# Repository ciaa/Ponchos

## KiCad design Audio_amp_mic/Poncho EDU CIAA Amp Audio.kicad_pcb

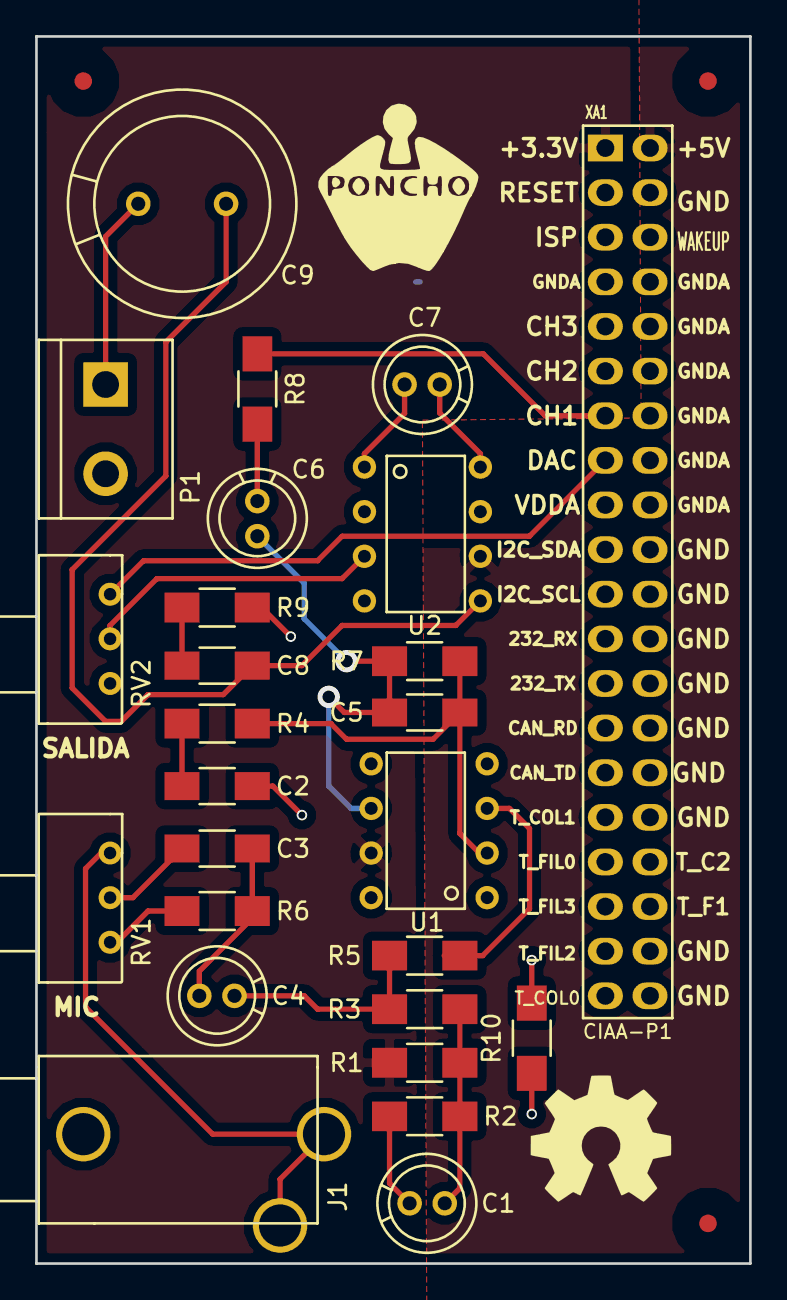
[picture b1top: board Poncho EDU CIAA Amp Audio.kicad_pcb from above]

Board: 2 copper layers, 40.6 x 69.8 mm, 30 parts (0 on the bottom side), 22 nets.

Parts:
C1: 100 uF; Kemet_ESH106M050AC3AA
C2: 22 uF; C_1206_HandSoldering
C3: 0,022 uF; C_1206_HandSoldering
C4: 1 uF; Kemet_ESH106M050AC3AA
C5: 100pF; C_1206_HandSoldering
C6, C7: 10 uF; Kemet_ESH106M050AC3AA
C8: 0,047 uF; C_1206_HandSoldering
C9: 270 uF; C_Kemet_ESY277M063AL3AA
F1, F2, F3: FIDUCIAL; Fiducial_1mm
G101: Logo_OSHWA
J1: JACK_2P; Conector_mini_Plug
P1: CONN_01X02; bornier2
R1, R2, R8: 4,7k; R_1206_HandSoldering
R3, R7: 47k; R_1206_HandSoldering
R4: 560; R_1206_HandSoldering
R5: 1k; R_1206_HandSoldering
R6: 15k; R_1206_HandSoldering
R9: 10; R_1206_HandSoldering
R10: 0; R_1206_HandSoldering
RV1: 20k; POT_20K_0.25W_Bourns_3310C
RV2: 10 k; POT_20K_0.25W_Bourns_3310C
U1: LM741; LM741_Texas_Instruments
U2: LM386; LM741_Texas_Instruments
XA1: Conn_Poncho2P_2x_20x2; Conn_Poncho_Derecha

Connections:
+3.3V: R1.1, U1.7, XA1.1
+5V: U2.6, XA1.2
/ADC: R8.1, XA1.13
/DAC: RV2.1, XA1.15
GND: R10.2, U1.4, U2.4, XA1.4, XA1.20, XA1.22, XA1.24, XA1.26, XA1.28, XA1.30, XA1.32, XA1.38, XA1.40
GNDA: C1.2, C2.2, J1.3, P1.2, R2.2, R6.1, R9.2, R10.1, RV1.3, RV2.3, U2.2, XA1.7, XA1.8, XA1.10, XA1.12, XA1.14, XA1.16, XA1.18
unnamed: C1.1, R1.2, R2.1, R3.2
unnamed: C2.1, R4.2
unnamed: C3.1, RV1.2
unnamed: C3.2, C4.1, R6.2
unnamed: C4.2, R3.1, R5.2
unnamed: C5.1, C6.1, R7.1, U1.6
unnamed: C5.2, R4.1, R7.2, U1.2
unnamed: C6.2, R8.2
unnamed: C7.1, U2.1
unnamed: C7.2, U2.8
unnamed: C8.1, C9.1, U2.5
unnamed: C8.2, R9.1
unnamed: C9.2, P1.1
unnamed: J1.1, J1.2, RV1.1
unnamed: R5.1, U1.3
unnamed: RV2.2, U2.3

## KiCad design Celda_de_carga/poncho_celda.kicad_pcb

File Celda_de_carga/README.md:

# LoadCellShield

Proyecto de modulo externo (Poncho) de una celda de carga para la EDU-CIAA, durante el curso de Diseño de PCB del CESE.

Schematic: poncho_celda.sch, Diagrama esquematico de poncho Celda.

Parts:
DS1: LCD16X2; LCD16x2
F1, F2, F3: FIDUCIAL; Fiducial_1mm
R7: 220; R_1206_HandSoldering
RV1: 10K; POT_SMD

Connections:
+5V: DS1.2, DS1.15, RV1.1; also elsewhere on the board
/Conector-EDU_CIAA/lcd1: DS1.11; also elsewhere on the board
/Conector-EDU_CIAA/lcd2: DS1.12; also elsewhere on the board
/Conector-EDU_CIAA/lcd3: DS1.13; also elsewhere on the board
/Conector-EDU_CIAA/lcd4: DS1.14; also elsewhere on the board
/Conector-EDU_CIAA/lcdEn: DS1.6; also elsewhere on the board
/Conector-EDU_CIAA/lcdRs: DS1.4; also elsewhere on the board
GND: DS1.1, DS1.5, DS1.7, DS1.8, DS1.9, DS1.10, R7.2, RV1.3; also elsewhere on the board
unnamed: DS1.3, RV1.2
unnamed: DS1.16, R7.1

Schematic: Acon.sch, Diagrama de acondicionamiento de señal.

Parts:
C1, C3: 1nF; C_0603_HandSoldering
C2: 10nF; C_0603_HandSoldering
C4, C5, C6: 100nF; C_0805_HandSoldering
R1, R2, R5, R6: 1k; R_1206_HandSoldering
R3: 499; R_1206_HandSoldering
R4: 51k; R_1206_HandSoldering
U1: AD620; SOIC-8
U2: REF1004-2.5; SOIC-8
U3: ADS1113/15; TSSOP-10_3x3mm_Pitch0.5mm
conn1: CONN_CELDA; bornier4

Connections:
+3.3V: R5.1, R6.1; also elsewhere on the board
+5V: C4.1, C5.1, C6.1, R4.2, U1.7, U3.8, conn1.1; also elsewhere on the board
/Adqui_Celda/alert: U3.2; also elsewhere on the board
/Adqui_Celda/scl: R5.2, U3.10; also elsewhere on the board
/Adqui_Celda/sda: R6.2, U3.9; also elsewhere on the board
GND: C1.1, C3.2, C4.2, C5.2, C6.2, U1.4, U2.4, U3.1, U3.3, conn1.4; also elsewhere on the board
unnamed: C1.2, C2.1, R1.1, U1.3
unnamed: C2.2, C3.1, R2.1, U1.2
unnamed: R1.2, conn1.2
unnamed: R2.2, conn1.3
unnamed: R3.1, U1.8
unnamed: R3.2, U1.1
unnamed: R4.1, U2.8
unnamed: U1.5, U2.6
unnamed: U1.6, U3.4

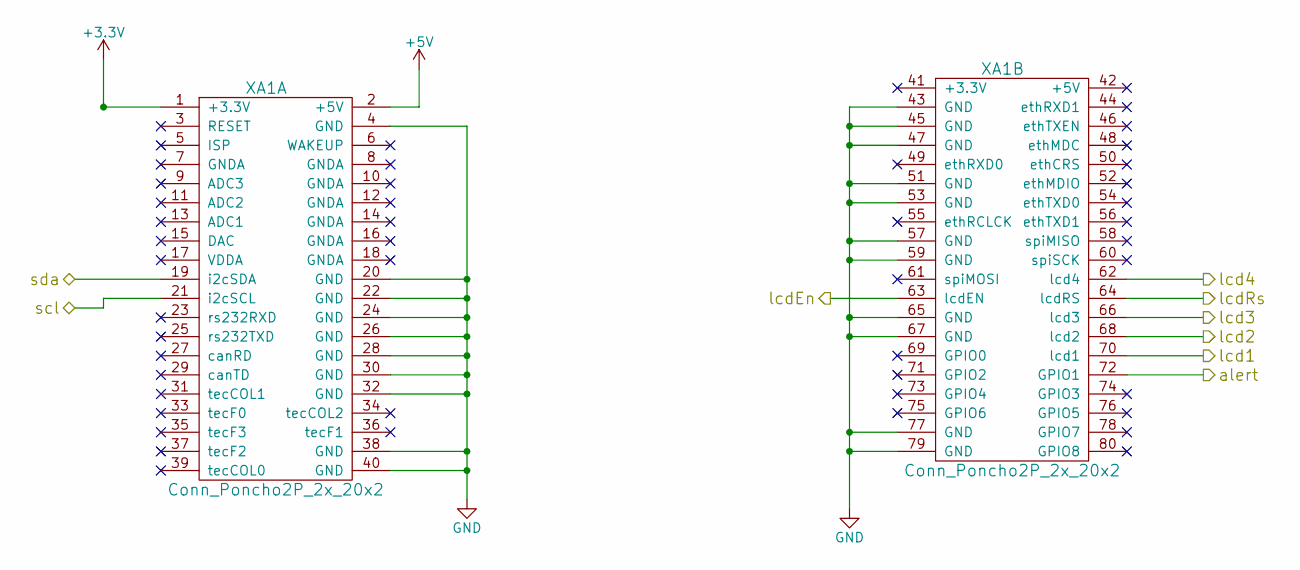
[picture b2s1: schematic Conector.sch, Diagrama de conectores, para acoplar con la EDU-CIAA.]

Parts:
XA1: Conn_Poncho2P_2x_20x2; Conn_Poncho_SinBorde

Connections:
+3.3V: XA1.1 (+3.3V); also elsewhere on the board
+5V: XA1.2 (+5V); also elsewhere on the board
/Adqui_Celda/alert: XA1.72 (GPIO1); also elsewhere on the board
/Adqui_Celda/scl: XA1.21 (i2cSCL); also elsewhere on the board
/Adqui_Celda/sda: XA1.19 (i2cSDA); also elsewhere on the board
/Conector-EDU_CIAA/lcd1: XA1.70 (lcd1); also elsewhere on the board
/Conector-EDU_CIAA/lcd2: XA1.68 (lcd2); also elsewhere on the board
/Conector-EDU_CIAA/lcd3: XA1.66 (lcd3); also elsewhere on the board
/Conector-EDU_CIAA/lcd4: XA1.62 (lcd4); also elsewhere on the board
/Conector-EDU_CIAA/lcdEn: XA1.63 (lcdEN); also elsewhere on the board
/Conector-EDU_CIAA/lcdRs: XA1.64 (lcdRS); also elsewhere on the board
GND: XA1.4 (GND), XA1.20 (GND), XA1.22 (GND), XA1.24 (GND), XA1.26 (GND), XA1.28 (GND), XA1.30 (GND), XA1.32 (GND), XA1.38 (GND), XA1.40 (GND), XA1.43 (GND), XA1.45 (GND), XA1.47 (GND), XA1.51 (GND), XA1.53 (GND), XA1.57 (GND), XA1.59 (GND), XA1.65 (GND), XA1.67 (GND), XA1.77 (GND), XA1.79 (GND); also elsewhere on the board

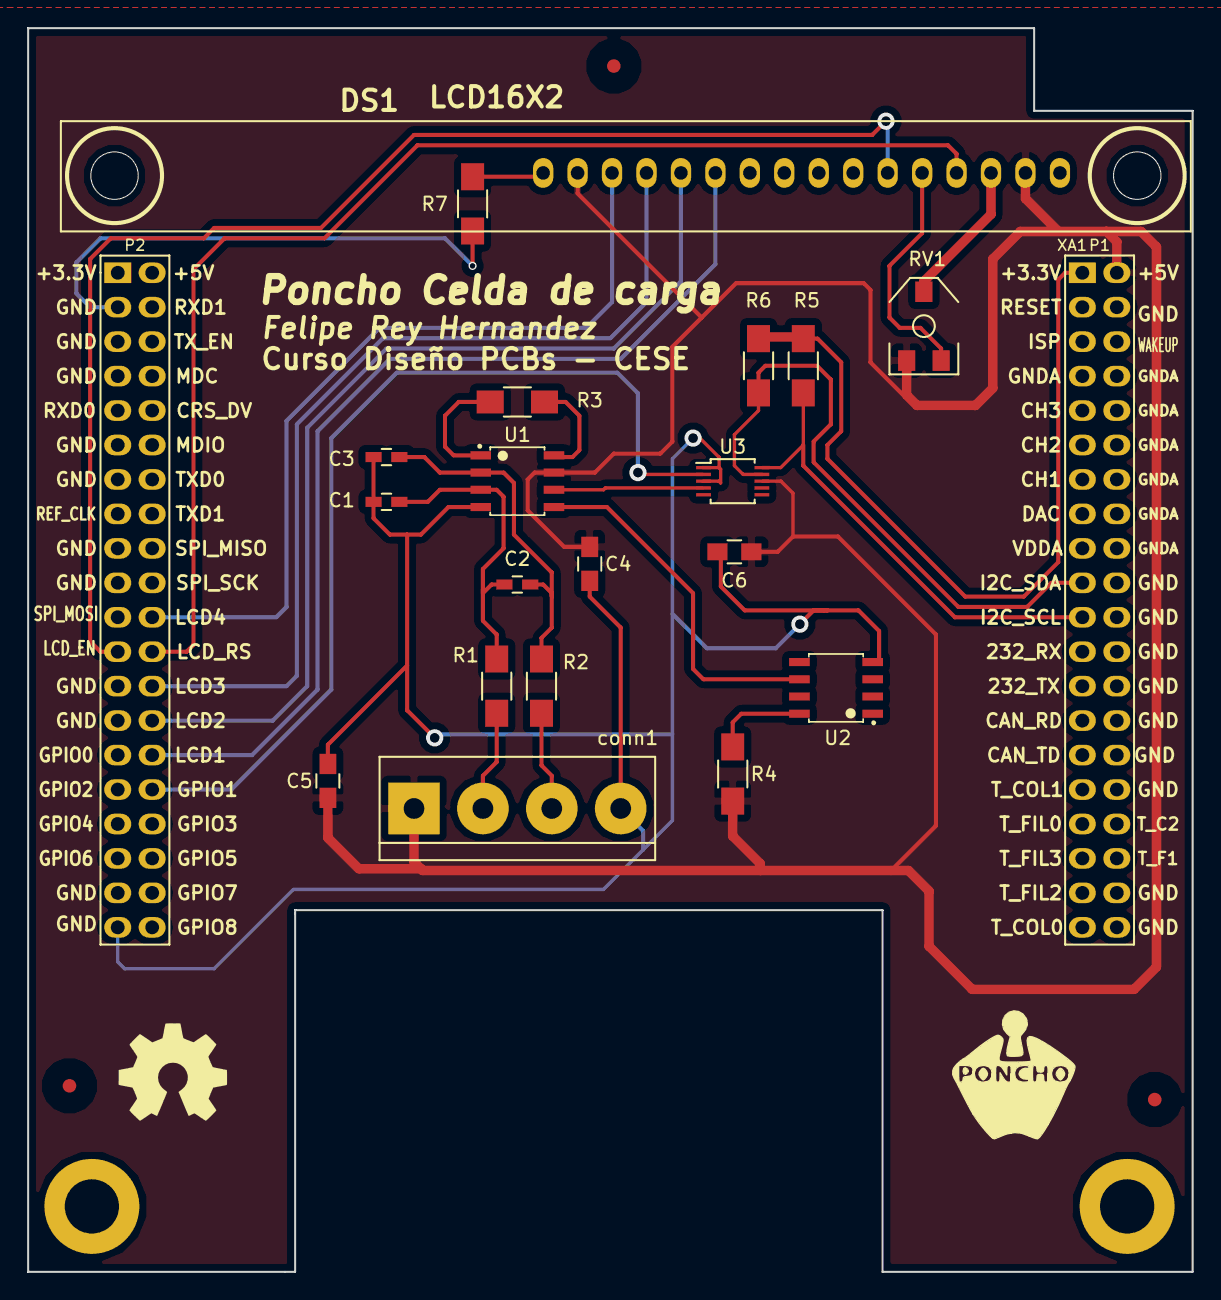
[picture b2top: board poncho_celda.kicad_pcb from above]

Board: 2 copper layers, 85.9 x 91.7 mm, 24 parts (0 on the bottom side), 23 nets.

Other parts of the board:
G101: Logo_OSHWA

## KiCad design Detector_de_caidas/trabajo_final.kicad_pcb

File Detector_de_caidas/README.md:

# fall_detector
Poncho para la plataforma CIAA con el cual se podrán detectar e informar caídas.

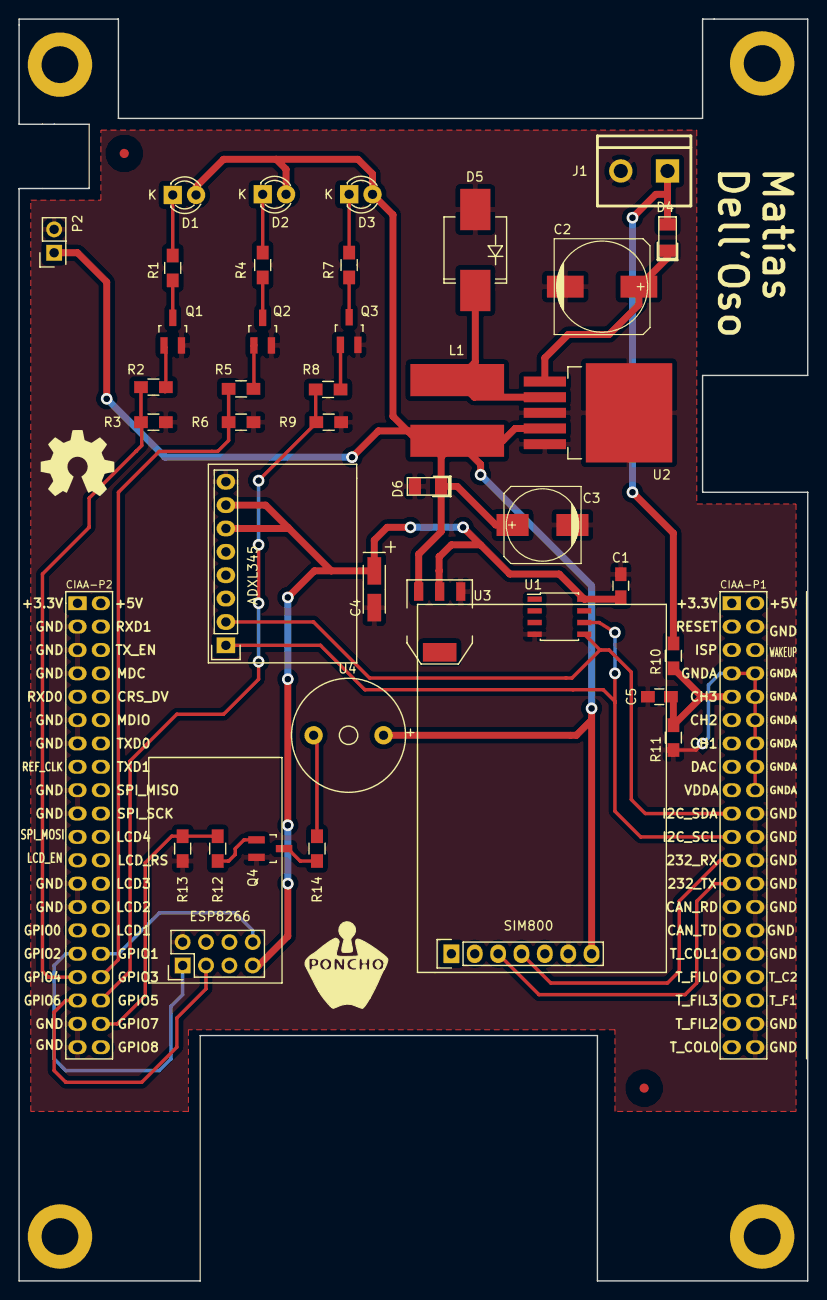
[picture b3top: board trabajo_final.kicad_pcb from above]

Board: 2 copper layers, 85.7 x 137.2 mm, 43 parts (0 on the bottom side), 30 nets.

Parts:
ADXL345: CONN_01X08; adxl345
C1, C5: 100nF; C_0805_HandSoldering
C2: 470uF; c2
C3: 330uF; c3
C4: 10uF; TantalC_SizeA_EIA-3216_HandSoldering
D1, D2, D3: LED; LED-3MM
D4: PMEG3020EH; SOD123F
D5: B540C-13-F; SMC_Handsoldering
D6: SMAZ5V6; SOD123F
ESP8266: CONN_02X04; esp8266
F1, F2: FIDUCIAL; Fiducial_1mm
G101: Logo_OSHWA
J1: TB_1X2; bornier2
L1: 47uH; SRN1060
P2: CONN_02X01; Pin_Header_Straight_2x01
Q1, Q2, Q3, Q4: 2N7002; SOT-23_Handsoldering
R1, R4, R7, R14: 680; R_0805_HandSoldering
R2, R5, R8, R12: 10K; R_0805_HandSoldering
R3, R6, R9, R13: 330K; R_0805_HandSoldering
R10: 470K; R_0805_HandSoldering
R11: 270K; R_0805_HandSoldering
SIM800: CONN_01X07; sim800l
U1: 24LC64; SOIC-8_3.9x4.9mm_Pitch1.27mm
U2: LM2596; TO-263-5Lead
U3: NCP1117ST33T3G; SOT-223
U4: Buzzer; Buzzer_12x9.5RM7.6
XA1: Conn_Poncho2P_2x_20x2; Conn_Poncho_Completo

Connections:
/Circuito Principal/ADC3: C5.2, R10.2, R11.1, XA1.9
/Circuito Principal/GPIO3: R5.2, R6.2, XA1.74
/Circuito Principal/GPIO4: R2.2, R3.2, XA1.73
/Circuito Principal/GPIO5: R8.2, R9.2, XA1.76
/Circuito Principal/GPIO6: ESP8266.3, XA1.75
/Circuito Principal/GPIO7: R12.1, R13.1, XA1.78
/Circuito Principal/RS232_RXD: SIM800.4, XA1.23
/Circuito Principal/RS232_TXD: SIM800.3, XA1.25
/Circuito Principal/SCL: ADXL345.1, U1.6, XA1.21
/Circuito Principal/SDA: ADXL345.2, U1.5, XA1.19
/Conector del Poncho/GPIO1: ESP8266.8, XA1.72
/Conector del Poncho/GPIO2: ESP8266.1, XA1.71
GND: ADXL345.8, C1.1, C2.2, C3.2, C4.2, C5.1, D5.1, D6.1, ESP8266.2, J1.2, P2.2, Q1.2, Q2.2, Q3.2, Q4.2, R3.1, R6.1, R9.1, R11.2, R13.2, SIM800.6, U1.4, U2.3, U2.5, U3.1, XA1.4, XA1.7, XA1.8, XA1.10, XA1.12, XA1.14, XA1.16, XA1.18, XA1.20, XA1.22, XA1.24, XA1.26, XA1.28, XA1.30, XA1.32, XA1.38, XA1.40, XA1.43, XA1.45, XA1.47, XA1.51, XA1.53, XA1.57, XA1.59, XA1.65, XA1.67, XA1.77, XA1.79
unnamed: C2.1, D4.2, U2.1
unnamed: D1.1, R1.2
unnamed: D2.1, R4.2
unnamed: D3.1, R7.2
unnamed: D4.1, J1.1, R10.1
unnamed: D5.2, L1.1, U2.2
unnamed: Q1.1, R2.1
unnamed: Q1.3, R1.1
unnamed: Q2.1, R5.1
unnamed: Q2.3, R4.1
unnamed: Q3.1, R8.1
unnamed: Q3.3, R7.1
unnamed: Q4.1, R12.2
unnamed: Q4.3, R14.2
unnamed: R14.1, U4.2
VCC: C3.1, D1.2, D2.2, D3.2, D6.2, L1.2, P2.1, SIM800.7, U2.4, U3.3, U4.1
VDD: ADXL345.6, ADXL345.7, C1.2, C4.1, ESP8266.7, U1.8, U3.2

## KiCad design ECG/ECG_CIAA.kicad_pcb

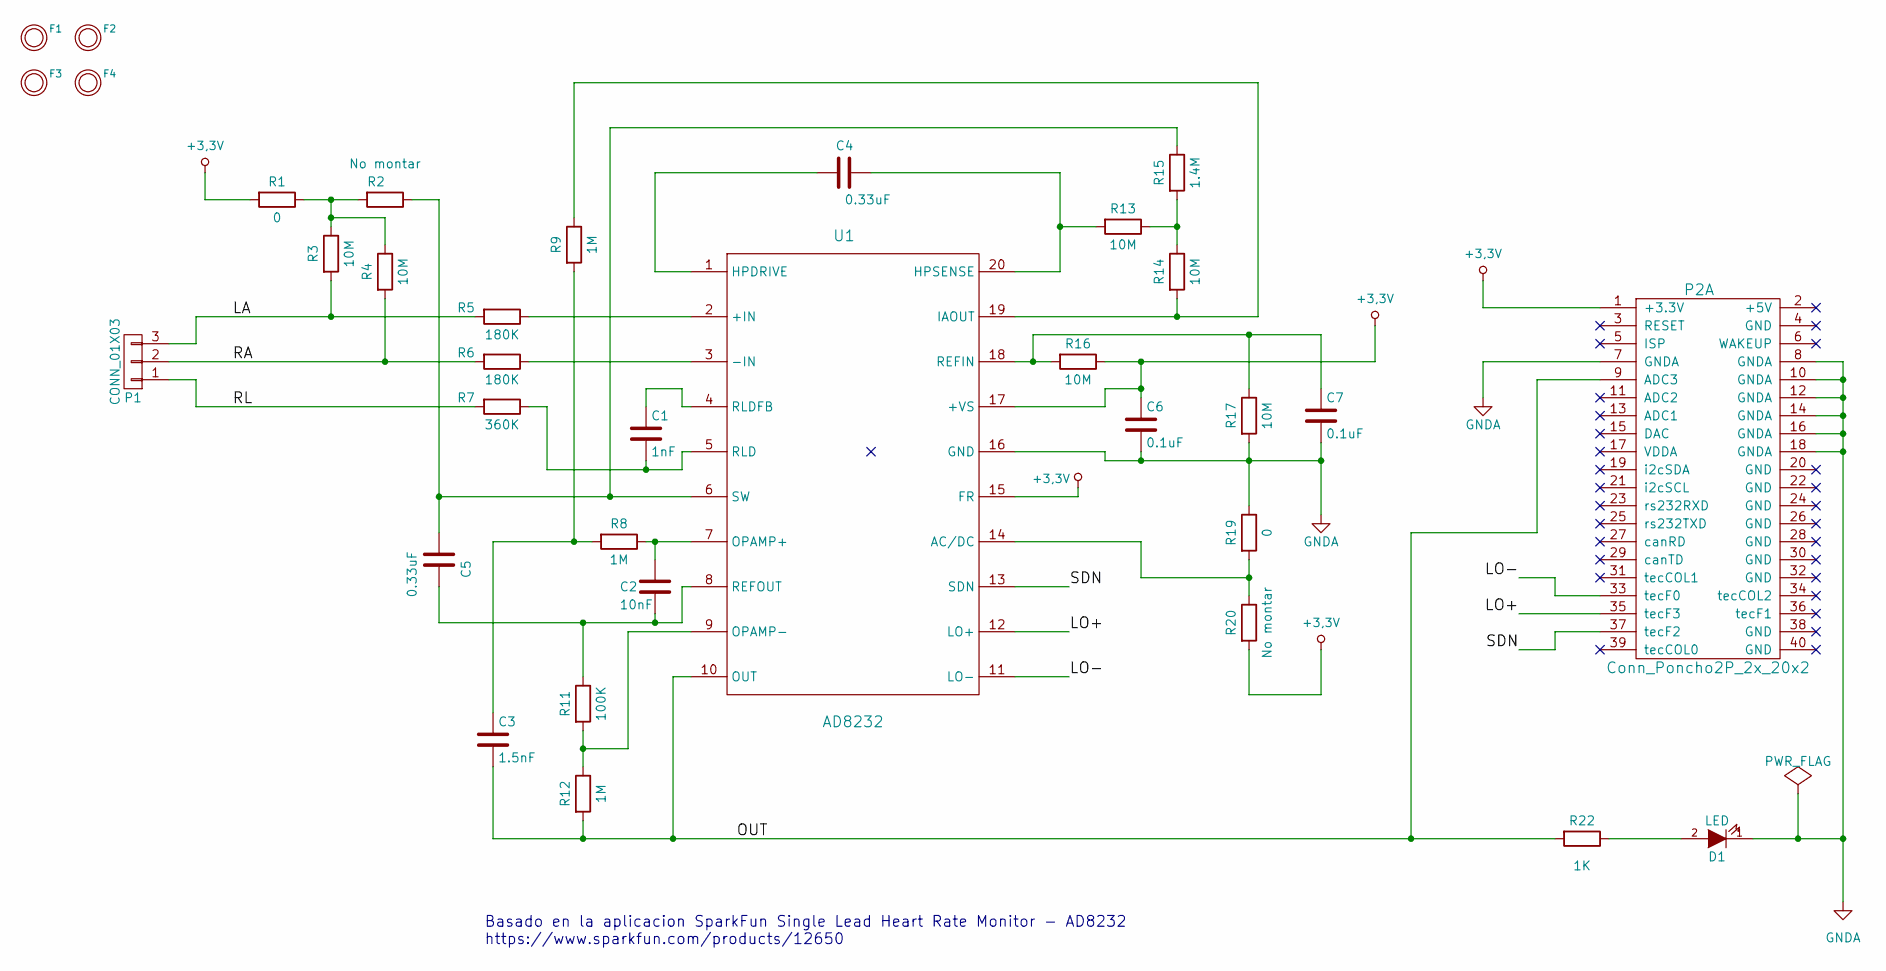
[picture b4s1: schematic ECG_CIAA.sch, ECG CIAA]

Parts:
C1: 1nF; C_0805; Digikey# 732-7813-2-ND
C2: 10nF; C_0805; Digikey# 732-8021-2-ND
C3: 1.5nF; C_0805; Digikey# 732-8018-2-ND
C4, C5: 0.33uF; C_0805; Digikey# 732-7651-2-ND
C6, C7: 0.1uF; C_0805; Digikey# 399-7999-2-ND
D1: LED; LED_0805; Digikey# 475-1410-2-ND
F1, F2, F3, F4: FIDUCIAL; Fiducial_1mm
P1: CONN_01X03; bornier3; Digikey# ED2601-ND
P2: Conn_Poncho2P_2x_20x2; Conn_Poncho_Derecha; Digikey# 609-2589-ND
R1, R19: 0; R_0805; Digikey# 311-0.0ARTR-ND
R2, R20: No montar; R_0805
R3, R4, R13, R14, R16, R17: 10M; R_0805; Digikey# RMCF0805JT10M0TR-ND
R5, R6: 180K; R_0805; Digikey# 311-180KARTR-ND
R7: 360K; R_0805; Digikey# 311-360KCRTR-ND
R8, R12: 1M; R_0805; Digikey# 311-1.00MCRTR-ND
R9: 1M; R_0805; Digikey# RHM1.0MBUTR-ND
R11: 100K; R_0805
R15: 1.4M; R_0805; Digikey# P1.4BTTR-ND
R22: 1K; R_0805; Digikey# 311-1.0KARTR-ND
U1: AD8232

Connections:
+3.3V: C6.1, P2.1 (+3.3V), R1.2, R16.1, R20.2, U1.15 (FR), U1.17 (+VS)
/LA: P1.3, R3.2, R5.2
/LO+: P2.35 (tecF3), U1.12 (LO+)
/LO-: P2.33 (tecF0), U1.11 (LO-)
/OUT: C3.2, P2.9 (ADC3), R12.2, R22.2, U1.10 (OUT)
/RA: P1.2, R4.2, R6.2
/RL: P1.1, R7.2
/SDN: P2.37 (tecF2), U1.13 (SDN)
GNDA: C6.2, C7.2, D1.1 (K), P2.7 (GNDA), P2.8 (GNDA), P2.10 (GNDA), P2.12 (GNDA), P2.14 (GNDA), P2.16 (GNDA), P2.18 (GNDA), R17.2, R19.1, U1.16 (GND)
unnamed: C1.1, U1.4 (RLDFB)
unnamed: C1.2, R7.1, U1.5 (RLD)
unnamed: C2.1, R8.1, U1.7 (OPAMP+)
unnamed: C2.2, C5.1, R11.1, U1.8 (REFOUT)
unnamed: C3.1, R8.2, R9.2
unnamed: C4.1, R13.2, U1.20 (HPSENSE)
unnamed: C4.2, U1.1 (HPDRIVE)
unnamed: C5.2, R2.1, R15.1, U1.6 (SW)
unnamed: C7.1, R16.2, R17.1, U1.18 (REFIN)
unnamed: D1.2 (A), R22.1
unnamed: R1.1, R2.2, R3.1, R4.1
unnamed: R5.1, U1.2 (+IN)
unnamed: R6.1, U1.3 (-IN)
unnamed: R11.2, R12.1, U1.9 (OPAMP-)
unnamed: R13.1, R14.1, R15.2
unnamed: R9.1, R14.2, U1.19 (IAOUT)
unnamed: R19.2, R20.1, U1.14 (AC/DC)

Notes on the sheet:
Basado en la aplicacion SparkFun Single Lead Heart Rate Monitor - AD8232 https://www.sparkfun.com/products/12650

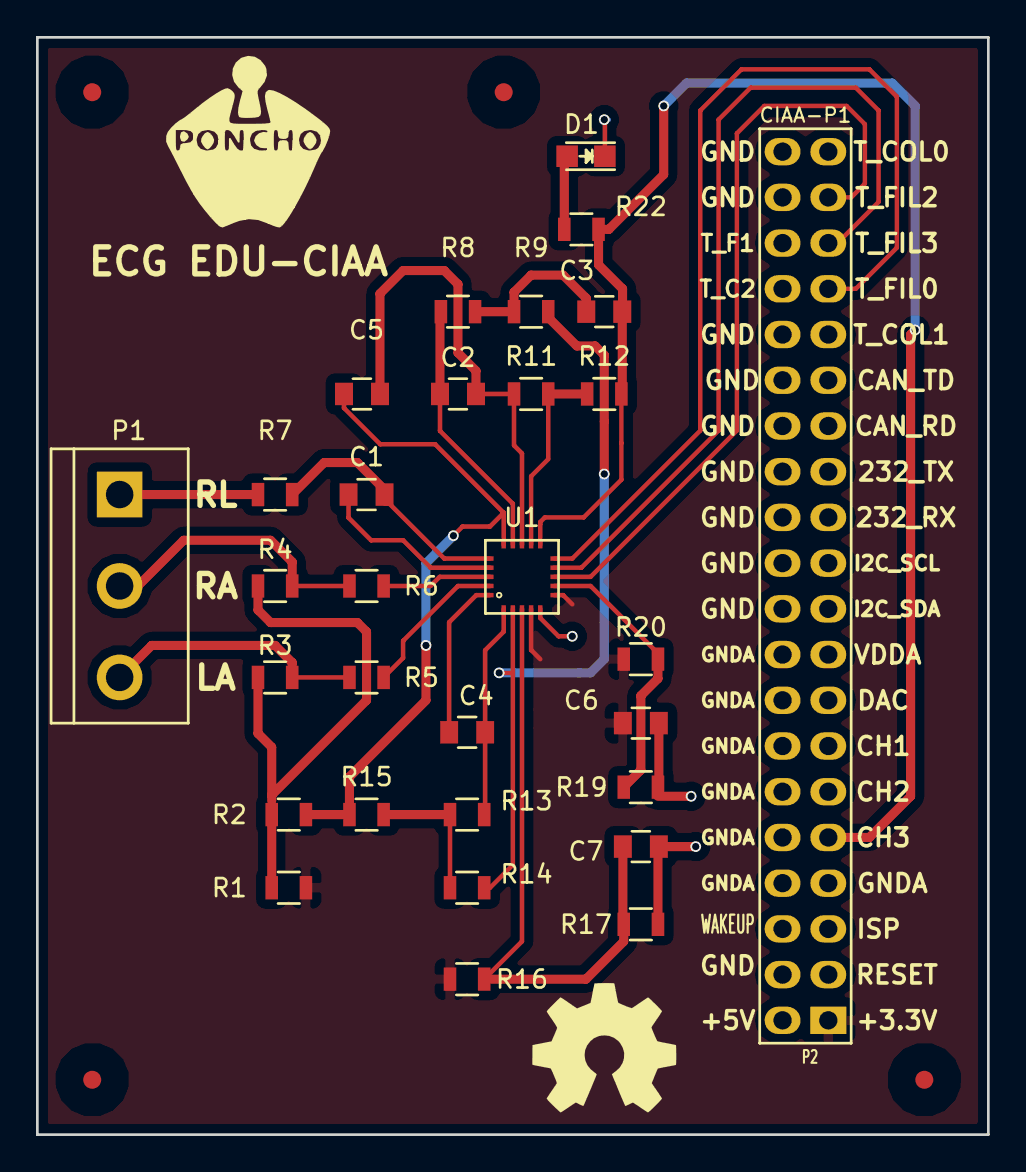
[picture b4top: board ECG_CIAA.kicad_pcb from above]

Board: 2 copper layers, 52.8 x 61.0 mm, 35 parts (0 on the bottom side), 26 nets.

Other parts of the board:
G101: Logo_OSHWA

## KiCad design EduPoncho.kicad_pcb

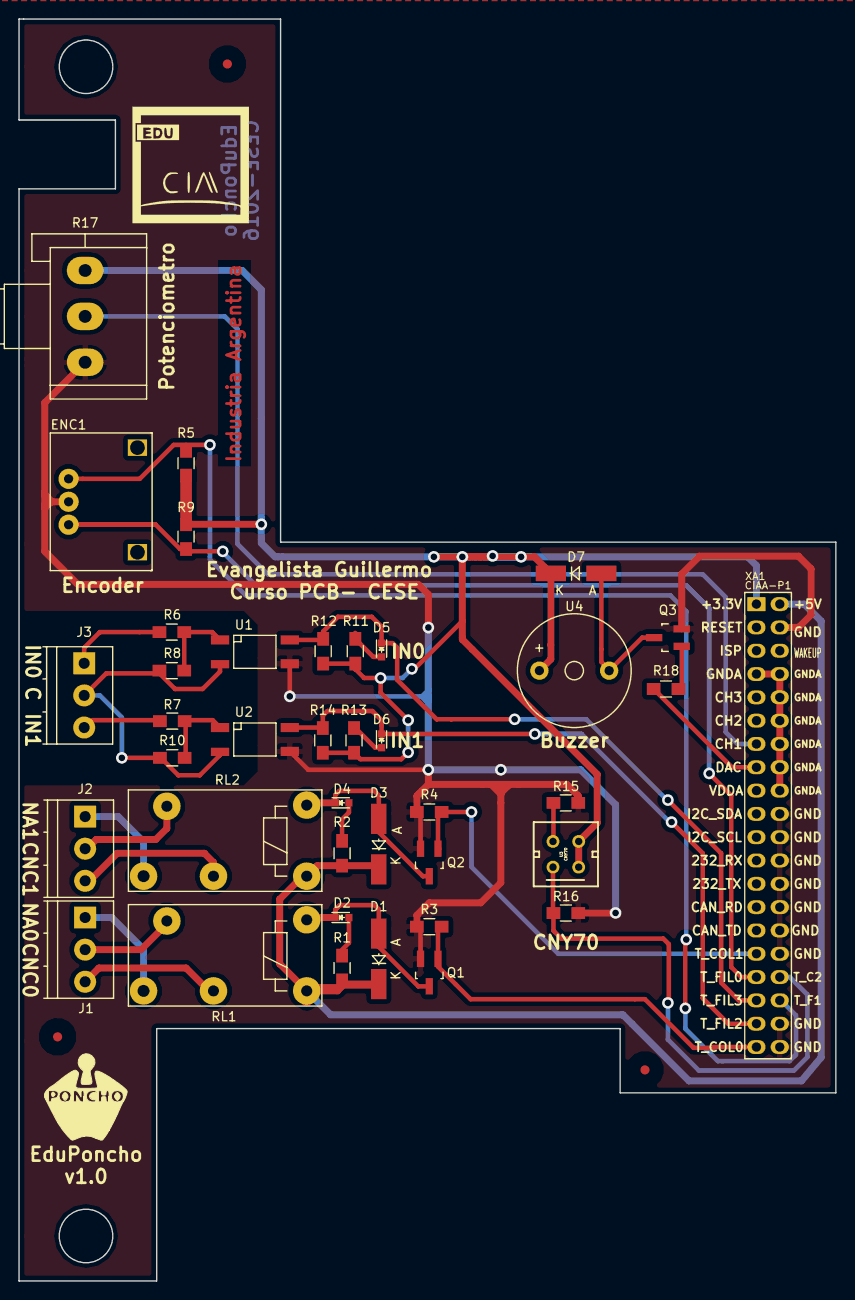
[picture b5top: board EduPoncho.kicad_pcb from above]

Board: 2 copper layers, 89.0 x 137.5 mm, 42 parts (0 on the bottom side), 33 nets.

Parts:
D1, D3, D7: LL4148; MiniMELF_Handsoldering
D2, D4: Led Rojo; LED_0603
D5, D6: Led Verde; LED_0603
ENC1: Encoder_rotativo
F?: Fiducial_1mm
F?#2, F?#3: Fiducial_1mm
J1, J2, J3: TB_1X3; TerminalBlock_Pheonix_PT-3.5mm_3pol
Q1, Q2: NDS7002A; SOT-23_Handsoldering
Q3: BC849; SOT-23_Handsoldering
R1, R2: 330; R_0805_HandSoldering
R3, R4, R12, R14: 100K; R_0805_HandSoldering
R5, R8, R9, R10, R16: 4K7; R_0805_HandSoldering
R6, R7, R18: 3K3; R_0805_HandSoldering
R11, R13: 2K2; R_0805_HandSoldering
R15: 220; R_0805_HandSoldering
R17: 5K; Potentiometer_Alps-RK16-single_largePads
RL1, RL2: G5Q-1; Relay_SPDT_Omron-G5-Q1
U1, U2: PS2805-1; Optocoupler_SMD_HandSoldering_KPC357_LTV35x_PC357_SingleCha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
U3: CNY70
U4: Buzzer; Buzzer_12x9.5RM7.6
XA1: Conn_Poncho2P_2x_20x2; Conn_Poncho_Derecha

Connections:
+3V3: D7.1, R5.1, R9.1, R11.1, R12.1, R13.1, R14.1, R17.3, U3.1, U3.4, U4.1, XA1.1
+5V: D1.1, D3.1, R1.2, R2.2, RL1.A1, RL2.A1, XA1.2
/Conector Poncho/Buzzer: R18.2, XA1.15
/Conector Poncho/CNY_IN: R16.1, U3.3, XA1.34
/Conector Poncho/Encoder_A: ENC1.1, R9.2, XA1.33
/Conector Poncho/Encoder_B: ENC1.3, R5.2, XA1.36
/Conector Poncho/GPIO0: Q1.1, R3.1, XA1.39
/Conector Poncho/GPIO1: Q2.1, R4.1, XA1.31
/Conector Poncho/OPTO_IN0: D5.1, R12.2, U1.4, XA1.35
/Conector Poncho/OPTO_IN1: D6.1, R14.2, U2.4, XA1.37
/Conector Poncho/Pote: R17.2, XA1.13
/Entradas/COM: J3.2, R8.2, R10.2, U1.2, U2.2
/Entradas/IN0: J3.1, R6.2
/Entradas/IN1: J3.3, R7.2
GND: ENC1.2, Q1.2, Q2.2, Q3.2, R3.2, R4.2, R15.2, R16.2, R17.1, U1.3, U2.3, XA1.4, XA1.20, XA1.22, XA1.24, XA1.26, XA1.28, XA1.30, XA1.32, XA1.38, XA1.40
GNDA: XA1.7, XA1.8, XA1.10, XA1.12, XA1.14, XA1.16, XA1.18
unnamed: D1.2, D2.1, Q1.3, RL1.A2
unnamed: D2.2, R1.1
unnamed: D3.2, D4.1, Q2.3, RL2.A2
unnamed: D4.2, R2.1
unnamed: D5.2, R11.2
unnamed: D6.2, R13.2
unnamed: D7.2, Q3.3, U4.2
unnamed: J1.1, RL1.14
unnamed: J1.2, RL1.11
unnamed: J1.3, RL1.12
unnamed: J2.1, RL2.14
unnamed: J2.2, RL2.11
unnamed: J2.3, RL2.12
unnamed: Q3.1, R18.1
unnamed: R6.1, R8.1, U1.1
unnamed: R7.1, R10.1, U2.1
unnamed: R15.1, U3.2

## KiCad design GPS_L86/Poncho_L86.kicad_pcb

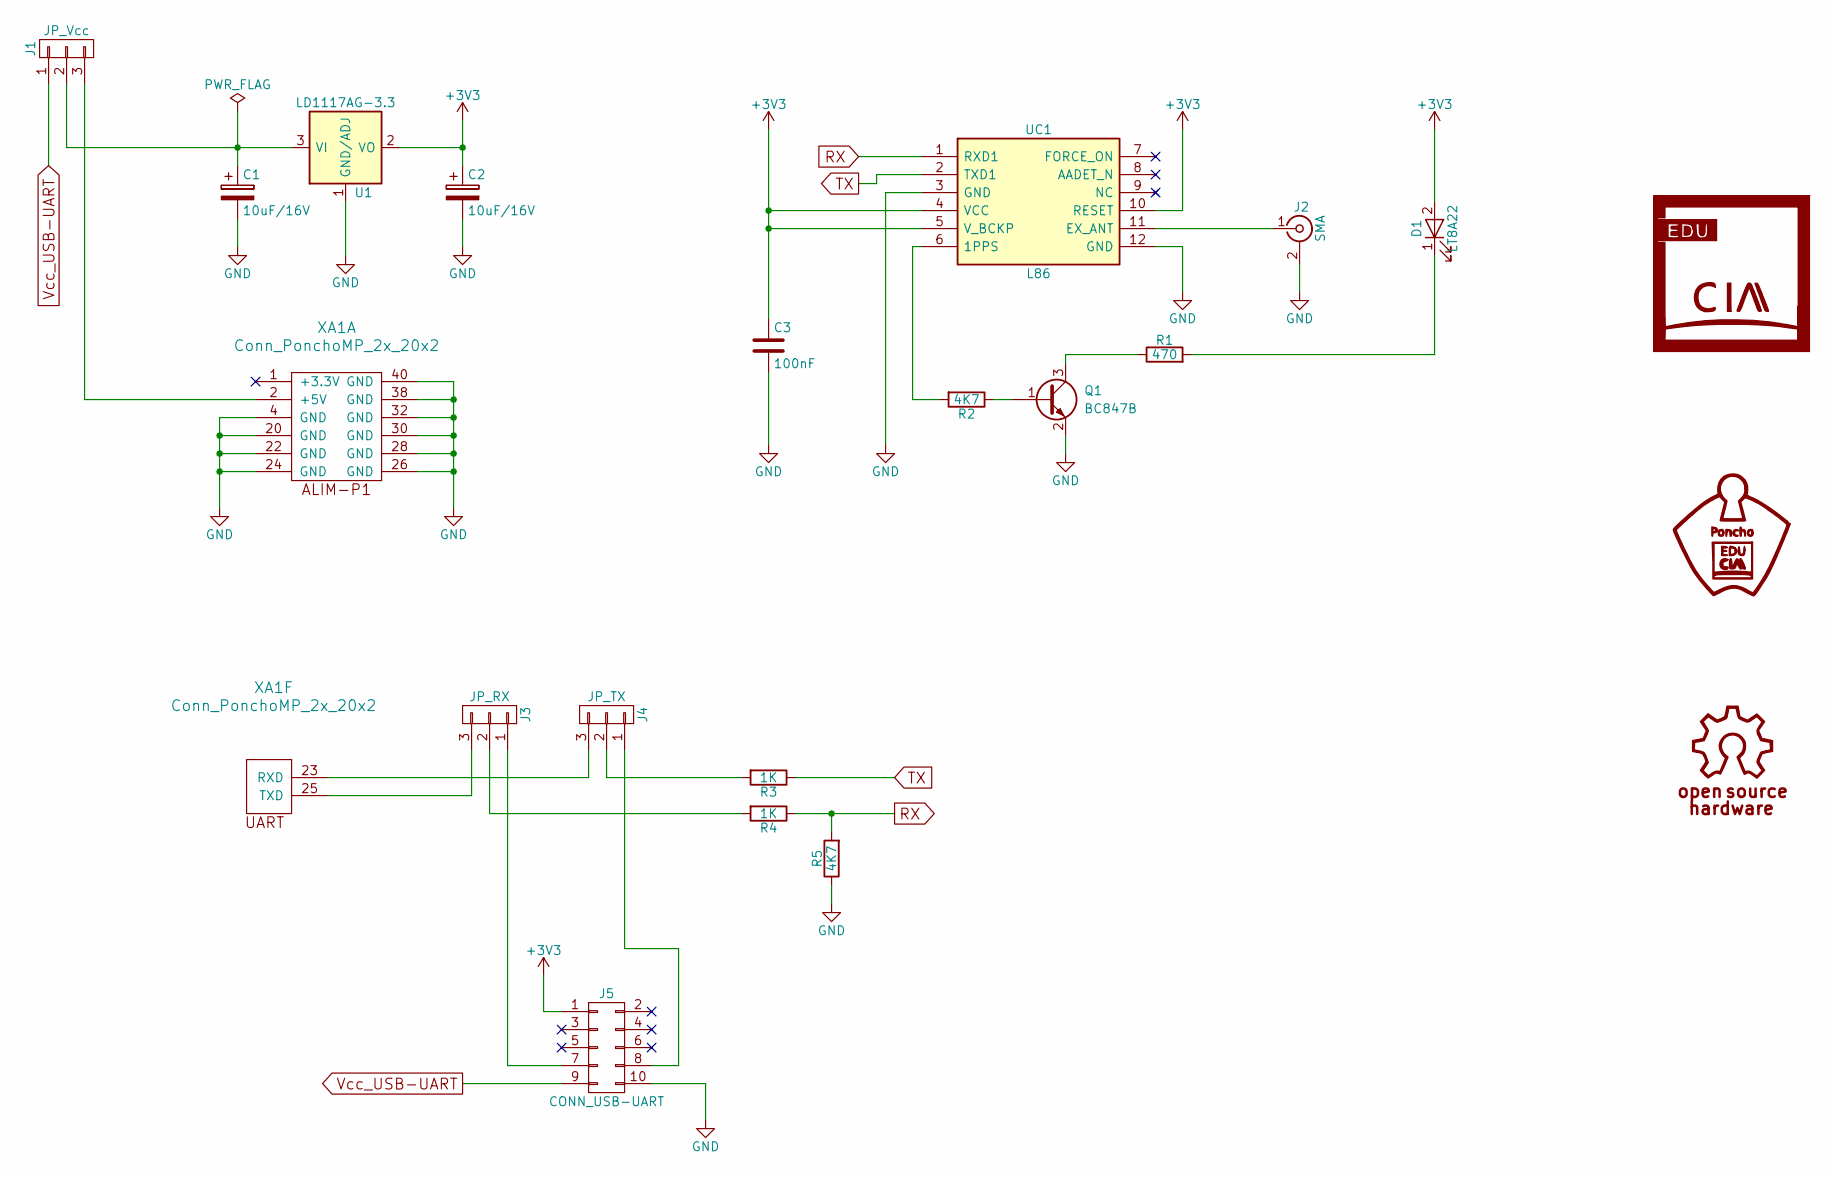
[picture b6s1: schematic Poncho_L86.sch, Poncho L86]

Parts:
C1, C2: 10uF/16V; CP_Elec_4x5.3
C3: 100nF; C_0805_HandSoldering
D1: LT8A22; LED_0805
J1: JP_Vcc; Pin_Header_Straight_1x03_Pitch2.54mm
J2: SMA; sma_90
J3: JP_RX; Pin_Header_Straight_1x03_Pitch2.54mm
J4: JP_TX; Pin_Header_Straight_1x03_Pitch2.54mm
J5: CONN_USB-UART; Socket_Strip_Angled_2x05_Pitch2.54mm
Q1: BC847B; SOT-23
R1: 470; R_0805_HandSoldering
R2, R5: 4K7; R_0805_HandSoldering
R3, R4: 1K; R_0805_HandSoldering
U1: LD1117AG-3.3; SOT-223
UC1: L86; Manufacturer_Part_Number L86
XA1: Conn_PonchoMP_2x_20x2; Conn_Poncho_Derecha_Sin_Pin_Desc

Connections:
+3V3: C2.1, C3.1, D1.2 (A), J5.1, U1.2 (VO), U1.4 (VO), UC1.4 (VCC), UC1.5 (V_BCKP), UC1.10 (RESET)
GND: C1.2, C2.2, C3.2, J2.2 (Ext), J5.10, Q1.2 (E), R5.1, U1.1 (GND/ADJ), UC1.3 (GND), UC1.12 (GND), XA1.4 (GND), XA1.20 (GND), XA1.22 (GND), XA1.24 (GND), XA1.26 (GND), XA1.28 (GND), XA1.30 (GND), XA1.32 (GND), XA1.38 (GND), XA1.40 (GND)
unnamed: C1.1, J1.2, U1.3 (VI)
unnamed: D1.1 (K), R1.2
unnamed: J1.3, XA1.2 (+5V)
unnamed: J2.1 (In), UC1.11 (EX_ANT)
unnamed: J3.1, J5.7
unnamed: J3.2, R4.2
unnamed: J3.3, XA1.25 (TXD)
unnamed: J4.1, J5.8
unnamed: J4.2, R3.2
unnamed: J4.3, XA1.23 (RXD)
unnamed: Q1.1 (B), R2.1
unnamed: Q1.3 (C), R1.1
unnamed: R2.2, UC1.6 (1PPS)
RX: R4.1, R5.2, UC1.1 (RXD1)
TX: R3.1, UC1.2 (TXD1)
Vcc_USB-UART: J1.1, J5.9

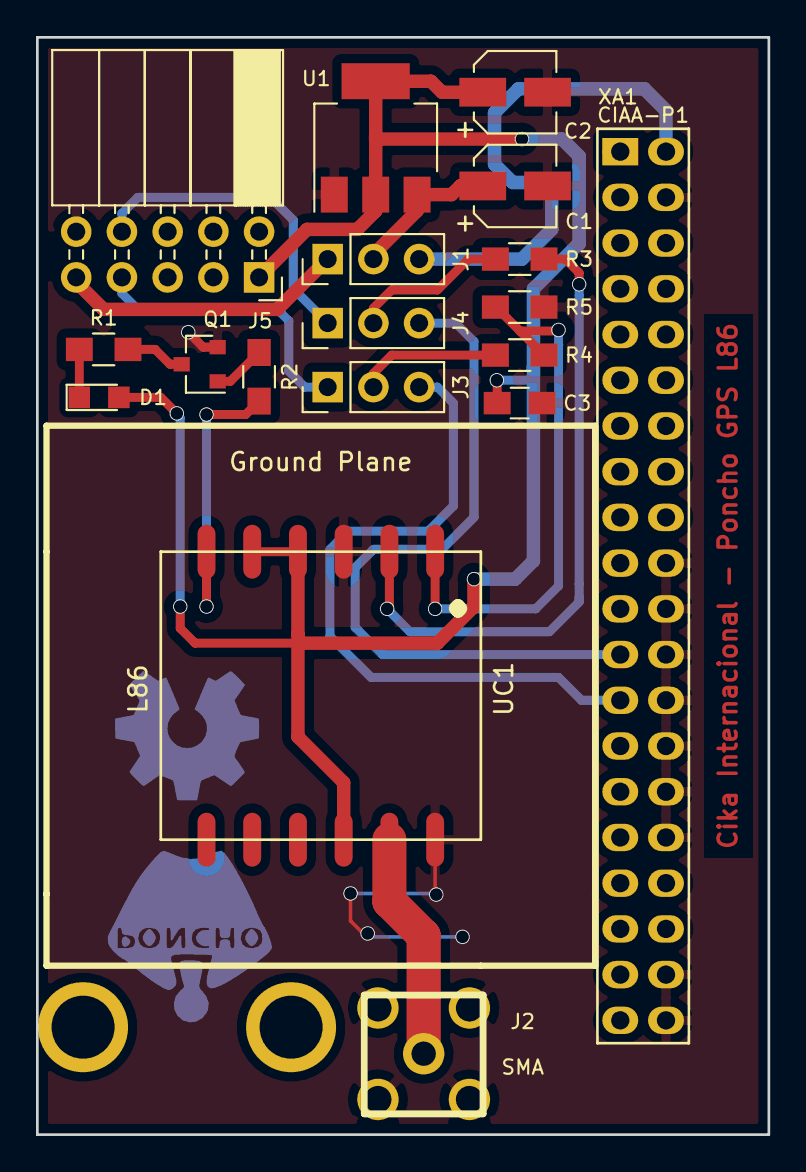
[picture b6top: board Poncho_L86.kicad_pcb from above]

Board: 2 copper layers, 40.6 x 61.0 mm, 20 parts (0 on the bottom side), 18 nets.

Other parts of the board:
H2, H2#2: PCB_HOLE; Led_Hole

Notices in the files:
Celda_de_carga/Acon.sch:
Licencia GPL V3
ECG/ECG_CIAA.kicad_pcb:
Licencia: https://creativecommons.org/licenses/by-sa/3.0/legalcode
